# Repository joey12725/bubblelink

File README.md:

# BubbleLink

**A wearable, pack-fed bubble system: one backpack feeds two hand-held bubble guns with power and solution, and a custom analog controller runs the pump only when you pull a trigger.**

Toy bubble guns are fun for about fifteen minutes. Then the AA cells sag, the bottle runs dry, and you are refilling a thimble of solution on a dark dance floor. BubbleLink moves the battery, the solution and the pump into a backpack and turns the guns into lightweight heads on umbilicals. Each umbilical carries power, a fluid line and a load-bearing tether. One 90 Wh pack and one litre of solution run two guns for a whole festival night.

Everything is here: the controller PCB (KiCad, Gerbers, BOM, pick-and-place, verification), every printed part (parametric OpenSCAD and ready-to-slice STLs), a full bill of materials, and build, bring-up and test guides.

| | | |
|:-:|:-:|:-:|
|  |  |  |
| **Duo guns**: a mirrored left/right pair, two blower heads each | **The stick**: battery sled, breaker, BMS and bucks over a draining wet cup | **BubbleLink CTRL v1.2**: 50 × 40 mm analog pump controller |

## Highlights

- **90 Wh 2S5P pack** (10 × Samsung 25R) with a 40 A BMS, USB-C charging, one 30 A manual-reset breaker and a pull-out power key.
- **Automatic pump control.** A Hall sensor sees gun current, a dual comparator turns the pump on, and an RC timer holds it for a tunable ~350 ms after the trigger releases. No firmware, no microcontroller, nothing to flash.
- **Two gun channels** on XT30U, each with its own fluid line and paracord tether. A dropped gun pulls on the cord, never the wires or the hose.
- **One shared peristaltic pump** with a recirculating bypass and check valve, so a stopped gun is never force-fed and the reservoir can't siphon.
- **Built for jumping.** The whole pack is one sealed upright "stick": dry tube on top, draining wet cup below, TPU seals and cushions, and nothing exits underneath.
- **Measured runtime**: about 2 hours of nonstop firing with all four heads, about 8 hours with one, and over 100 hours idle.
- **Verified before fabrication.** 50 automated release checks on the board files and a 20,000-sample Monte Carlo of the analog circuit, both re-runnable from this repo.
- **56 ready-to-slice STLs**, all watertight and designed to print without supports, generated from parametric OpenSCAD.

## How it works

```mermaid
flowchart LR
    subgraph pack["Backpack: the stick"]
        BAT["2S5P 90 Wh<br/>+ 40 A BMS"] --> KEY["Power key<br/>(XT60H)"] --> BRK["30 A breaker"] --> ACS["ACS758<br/>current sensor"]
        ACS --> CH1["Gun port 1<br/>XT30U"]
        ACS --> CH2["Gun port 2<br/>XT30U"]
        BRK --> BUCKA["Buck A 5 V"] --> CTRL["BubbleLink CTRL<br/>analog controller"]
        ACS -. "40 mV/A" .-> CTRL
        CTRL --> PUMP["G528 peristaltic pump"]
        BLAD["1 L bladder"] --> PUMP --> TEE["Tees + bypass<br/>+ check valve"]
    end
    CH1 == "power + hose + tether" ==> G1["Duo gun L"]
    CH2 == "power + hose + tether" ==> G2["Duo gun R"]
    TEE --> G1
    TEE --> G2
```

1. **Pull a trigger.** The gun's motor draws current straight from the battery bus (6.0–8.4 V, unregulated). Gun current never passes through the PCB.
2. **The controller notices.** The ACS758 module reports combined gun current. One half of the TLV1822 comparator flags it against the RV1 threshold.
3. **The pump runs.** Q1 charges a hold capacitor, the second comparator half sees it high and (through Q3) turns on the AO3400A pump MOSFET, and the G528 pushes solution down both umbilicals.
4. **Release the trigger.** The hold capacitor bleeds through RV2, with Schmitt feedback for a clean edge. About 350 ms later the pump stops, so the donor pumps in the heads stay primed without flooding.
5. **Prime on demand.** The PRIME button on the cap runs the same timed path, for filling lines at the start of a night.

Every failure lands on "pump off": a supervisor clamps the timer below 4.38 V, the pump gate defaults low if the comparator is unpowered, a PTC guards the pump branch, and an unplugged sensor reads as no current. The [design description](hardware/pcb/BubbleLink_CTRL_v1_2_PCBWay/customer/DESIGN_DESCRIPTION.md) walks through every net.

## Repository layout

| Path | Contents |
|---|---|
| [`hardware/pcb/BubbleLink_CTRL_v1_2_PCBWay/`](hardware/pcb/BubbleLink_CTRL_v1_2_PCBWay/) | Controller release: KiCad source, Gerbers, SMT BOM/CPL, assembly drawing, schematic, verification |
| [`hardware/pcb/hand_solder_guide/`](hardware/pcb/hand_solder_guide/) | Illustrated guides for the through-hole parts, harness, battery and first power-up |
| [`hardware/printed/`](hardware/printed/README.md) | OpenSCAD sources (`src/`), STLs (`stl/`), renders and the full print guide |
| [`docs/`](docs/canonical-facts.md) | System design, subsystems, build guide, test plan, BOM |
| [`tests/`](tests/) | Release checks run in CI |

## Build one

1. **Get the parts.** Everything is in the [bill of materials](docs/bom.md), with part numbers and supplier search links.
2. **Order the board.** Upload [`BubbleLink_CTRL_v1_2_Gerbers.zip`](hardware/pcb/BubbleLink_CTRL_v1_2_PCBWay/fabrication/BubbleLink_CTRL_v1_2_Gerbers.zip) with the SMT [BOM](hardware/pcb/BubbleLink_CTRL_v1_2_PCBWay/assembly/PCBWAY_SMT_BOM.csv) and [CPL](hardware/pcb/BubbleLink_CTRL_v1_2_PCBWay/assembly/PCBWAY_SMT_CPL.csv) to any fab with top-side assembly. Hand-solder the ten through-hole parts using the [solder guide](hardware/pcb/hand_solder_guide/).
3. **Print the parts.** Start with the fit coupons, then follow the [print order](hardware/printed/README.md#print-order). Rigid parts are ASA, seals and cushions are TPU, and nothing needs supports.
4. **Assemble.** The [build guide](docs/10-build-guide.md) covers cell matching, the 2S5P block, the harness, sled, cup plumbing, umbilicals and the guns.
5. **Bring it up.** Follow the [bring-up and acceptance test](docs/07-pcb/bringup-and-acceptance-test.md) to set the detection threshold (RV1) and the off-delay (RV2), then run the [system test plan](docs/13-test-plan.md).

### Firmware

There isn't any. The controller is pure analog: two trimmers set its behaviour, and a multimeter and a screwdriver are the whole toolchain.

### Rebuilding the printed parts

```sh
cd hardware/printed
./build.sh /path/to/openscad      # regenerates every STL from src/ (OpenSCAD 2024+ with the manifold backend)
python check_stl.py               # watertight, one body, no overhang past 45°
```

## Verify the release

The checks that gate the PCB release and the printed parts run in CI on every push:

```sh
pip install -r requirements-dev.txt
python -m pytest -q
```

That covers the release checksums, the 50-check manufacturing validator (board outline, nets, holes, BOM, CPL, DRC, frozen hashes), the analog model with a Monte Carlo sweep, and watertightness of every STL. The full 20,000-sample run is `python3 hardware/pcb/BubbleLink_CTRL_v1_2_PCBWay/verification/analog_model/run_verification.py`.

## Documentation

**System:** [canonical facts](docs/canonical-facts.md) (the one-page source of truth) · [overview and requirements](docs/01-overview-and-requirements.md) · [architecture](docs/02-system-architecture.md) · [design decisions](docs/03-design-decisions.md) · [glossary](docs/glossary.md)

**Subsystems:** [power](docs/04-power-system.md) · [fluid](docs/05-fluid-system.md) · [guns, heads and umbilicals](docs/06-guns-heads-and-umbilicals.md) · [controller PCB](docs/07-pcb/overview.md) ([pinout](docs/07-pcb/connectors-and-pinout.md), [BOM](docs/07-pcb/bom-and-parts.md), [fabrication](docs/07-pcb/fabrication-and-assembly.md), [bring-up](docs/07-pcb/bringup-and-acceptance-test.md), [revisions](docs/07-pcb/revision-history.md)) · [printed parts](docs/09-printed-parts.md)

**Making it:** [BOM](docs/bom.md) · [build guide](docs/10-build-guide.md) · [test plan](docs/13-test-plan.md) · [roadmap](docs/16-roadmap-future-extensions.md)

## Tech

KiCad 9 · tscircuit · Gerbonara + Shapely geometry checks · Python analog model with Monte Carlo · OpenSCAD (manifold backend) · trimesh · ASA and TPU on a Creality K2 Plus and a Bambu Lab A1

## Safety

This is a 90 Wh lithium pack worn on your back. Build the battery with matched cells, keep the breaker in the + line, charge with the cap off until you have checked enclosed-charging temperature, and follow the bench gates in the test plan before wearing it.

## License

Open hardware. Hardware design files are [CERN-OHL-P-2.0](LICENSES/CERN-OHL-P-2.0.txt), software is [MIT](LICENSES/MIT.txt), and documentation and images are [CC-BY-4.0](LICENSES/CC-BY-4.0.txt). See [LICENSE](LICENSE) for which applies where.

---

Designed and built by **Joey Hersh**.

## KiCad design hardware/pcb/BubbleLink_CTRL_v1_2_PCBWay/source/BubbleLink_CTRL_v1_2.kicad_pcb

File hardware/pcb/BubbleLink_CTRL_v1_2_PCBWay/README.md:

# BubbleLink CTRL v1.2: release package

The complete fabrication release for the BubbleLink pump controller: a 50 × 40 mm, two-layer, all-analog board that runs the pack's transfer pump whenever a gun draws current, then holds it on for a tunable off-delay.

## Ordering boards

Upload these to any PCB fab that does top-side SMT assembly:

| File | Use |
|---|---|
| `fabrication/BubbleLink_CTRL_v1_2_Gerbers.zip` | Gerbers and drills. Upload this ZIP, not the whole folder |
| `assembly/PCBWAY_SMT_BOM.csv` | SMT BOM (41 placements, top side only) |
| `assembly/PCBWAY_SMT_CPL.csv` | Pick-and-place, mm, lower-left datum, top view |
| `assembly/ASSEMBLY_NOTES_FOR_PCBWAY.txt` | Polarity, DNP and substitution rules |
| `drawings/BubbleLink_CTRL_v1_2_Assembly_and_U1_Detail.pdf` | Assembly drawing; its numbered pads and pin-1 table control orientation |
| `assembly/CRITICAL_PAD1_COORDINATES.csv` | Pin-1 coordinates for U1, U2, Q1–Q3, D1 |

J4 and R22 are DNP. C9 and R18 must be fitted. U1 is TI TLV1822QDRQ1 with no substitute. The through-hole parts (`assembly/USER_THT_BOM.csv`) are hand-soldered after delivery; see the [hand-solder guide](../hand_solder_guide/).

## What else is here

- `source/`: KiCad project (`.kicad_pcb`, `.kicad_sch`, `.kicad_pro`, also zipped), the serialized tscircuit design, and `repro/`, the deterministic engineering-change scripts that turn the v1.1 baseline into v1.2.
- `drawings/`: schematic and PCB SVGs and independently parsed Gerber previews.
- `customer/`: design description, bring-up and acceptance test, motor harness suppression.
- `verification/`: the analog model with Monte Carlo, the manufacturing QA validator, DRC results and geometry regression.
- `ENGINEERING_CHANGE_AND_REVIEW.md`: why v1.2 exists (the corrected U1 land pattern, per TI D0008A) and what changed.
- `SHA256SUMS.txt`: checksums for every file in this folder.

## Re-running the checks

```sh
python3 verification/manufacturing_qa/validate_release.py --help   # or:
bash verification/run_release_qa.sh                                  # 50 structural checks
python3 verification/analog_model/run_verification.py               # model + 20,000-sample Monte Carlo
python3 verification/verify_eco.py                                   # needs gerbonara + shapely
```

The automated checks cover structure, geometry and the circuit model. Startup, brownout, timing calibration, sensor noise and thermal behaviour are covered by the bench procedure in `customer/BRINGUP_AND_ACCEPTANCE_TEST.md`.

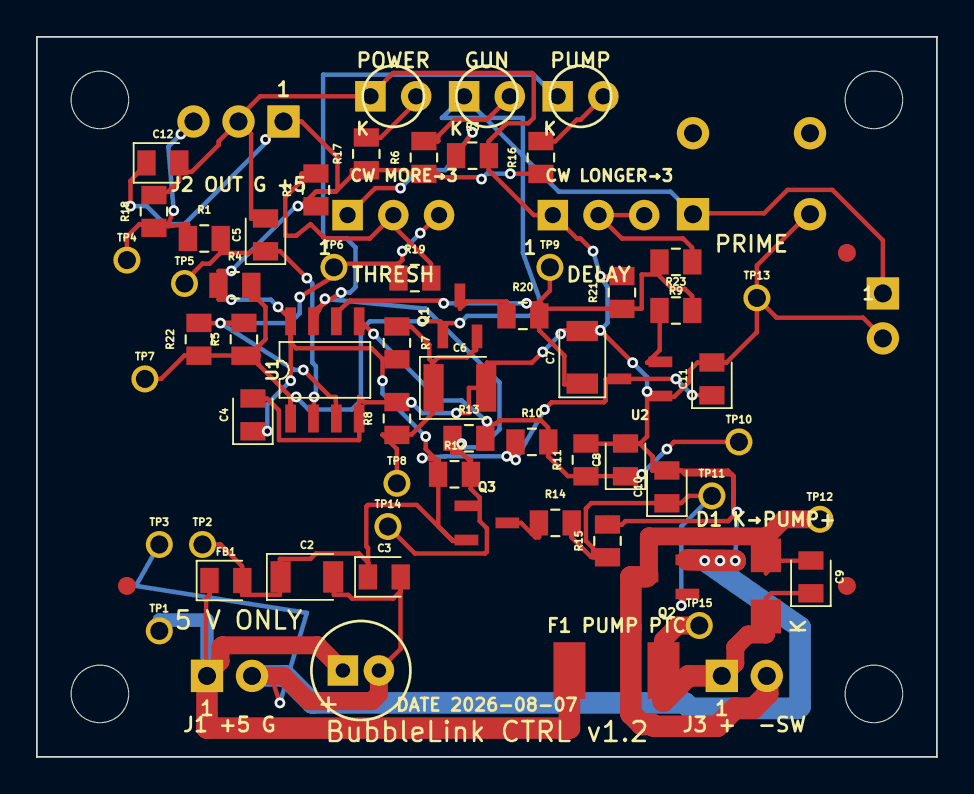
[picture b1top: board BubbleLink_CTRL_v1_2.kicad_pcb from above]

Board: 2 copper layers, 50.0 x 40.0 mm, 68 parts (0 on the bottom side), 23 nets.

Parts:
C1: 16ZLH100MEFC5X11
C2: 10uF; GRM31CR71C106KA12L
C3, C4, C8, C9, C10, C11, C12: 100nF; GRM21BR71H104KA01L
C5: 1uF; GRM21BR71C105KA01L
C6: 22uF; C3225X7R1E226M250AB
C7: 6.8uF; CGA5L1X7R1E685K160AC
D1: B340A-E3/61T; B340A-E3_61T
F1: F1; 1812L150_16DR
FB1: BLM21PG221SN1D
J1, J3: B2B-XH-A(LF)(SN)
J2: B3B-XH-A(LF)(SN)
J4: chip
LED1: L-934GD
LED2: L-934YD
LED3: L-934ID
Q1, Q3: DMP2065UQ-7
Q2: AO3400A
R1, R4, R9, R11, R12, R15: 10kΩ; RC0805FR-0710KL
R2, R3: 7.5kΩ; RC0805FR-077K5L
R5, R13, R22: 4.7MΩ; RC0805FR-074M7L
R6, R16, R17, R20: 2.2kΩ; RC0805FR-072K2L
R7, R8: 4.7kΩ; RC0805FR-074K7L
R10: 39kΩ; RC0805FR-0739KL
R14: 100Ω; RC0805FR-07100RL
R18: 100kΩ; RC0805FR-07100KL
R19: 220kΩ; RC0805FR-07220KL
R21: 1MΩ; RC0805FR-071ML
R23: 560Ω; RC0805FR-07560RL
RV1: 3296W-1-202LF
RV2: 3296W-1-104LF
SW1: B3F-1000
TP1: TP1; test_point_platedhole_d1
TP2: TP2; test_point_platedhole_d1
TP3: TP3; test_point_platedhole_d1
TP4: TP4; test_point_platedhole_d1
TP5: TP5; test_point_platedhole_d1
TP6: TP6; test_point_platedhole_d1
TP7: TP7; test_point_platedhole_d1
TP8: TP8; test_point_platedhole_d1
TP9: TP9; test_point_platedhole_d1
TP10: TP10; test_point_platedhole_d1
TP11: TP11; test_point_platedhole_d1
TP12: TP12; test_point_platedhole_d1
TP13: TP13; test_point_platedhole_d1
TP14: TP14; test_point_platedhole_d1
TP15: TP15; test_point_platedhole_d1
U1: TLV1822QDRQ1
U2: TLV803EA43DBZR

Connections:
.F1 > .pin2 to .J3 > .pin1: C9.1, D1.1, F1.2, J3.1, TP15.1
.FB1 > .pin2 to .C2 > .pin1: C2.1, C3.1, C4.1, C11.1, C12.1, FB1.2, J2.1, Q3.2, R2.1, R4.1, R6.1, R7.1, R10.1, R12.1, R16.1, R17.1, TP2.1, U1.8, U2.3
.J1 > .pin1 to .F1 > .pin1: C1.1, F1.1, FB1.1, J1.1, TP1.1
.J1 > .pin2 to .Q2 > .pin2: C1.2, C2.2, C3.2, C4.2, C5.2, C6.2, C7.2, C8.2, C10.2, C11.2, C12.2, J1.2, J2.2, J4.2, LED1.1, Q2.2, R3.2, R8.2, R11.2, R15.2, R18.2, R21.2, RV2.1, SW1.3, TP3.1, TP13.1, U1.4, U2.1
.J2 > .pin3 to .R18 > .pin1: J2.3, R1.1, R18.1, TP4.1
.Q1 > .pin3 to .R20 > .pin1: Q1.3, R20.1
.Q2 > .pin3 to .J3 > .pin2: C9.2, D1.2, J3.2, Q2.3, TP12.1
.Q3 > .pin3 to .R14 > .pin1: Q3.3, R14.1
.R1 > .pin2 to .C5 > .pin1: C5.1, R1.2, TP5.1, U1.2
.R2 > .pin2 to .RV1 > .pin3: R2.2, R19.2, RV1.3
.R6 > .pin2 to .LED2 > .pin2: LED2.2, R6.2
.R7 > .pin2 to .C6 > .pin1: C6.1, Q1.2, R7.2, R8.1, TP8.1
.R9 > .pin2 to .RV2 > .pin3: R9.2, RV2.2, RV2.3
.R14 > .pin2 to .R15 > .pin1: C10.1, Q2.1, R14.2, R15.1, TP11.1
.R16 > .pin2 to .LED3 > .pin2: LED3.2, R16.2
.R17 > .pin2 to .LED1 > .pin2: LED1.2, R17.2
.RV1 > .pin1 to .R3 > .pin1: R3.1, RV1.1
.RV1 > .pin2 to .R19 > .pin1: R5.2, R19.1, R22.2, RV1.2, TP6.1, U1.3
.U1 > .pin1 to .R5 > .pin1: J4.1, LED2.1, Q1.1, R4.2, R5.1, R22.1, SW1.1, TP7.1, U1.1
.U1 > .pin5 to .R13 > .pin2: C8.1, R10.2, R11.1, R13.2, TP10.1, U1.5
.U1 > .pin6 to .R20 > .pin2: C7.1, R9.1, R20.2, R21.1, R23.2, TP9.1, U1.6
.U1 > .pin7 to .R13 > .pin1: LED3.1, Q3.1, R12.2, R13.1, TP14.1, U1.7
.U2 > .pin2 to .R23 > .pin1: R23.1, U2.2

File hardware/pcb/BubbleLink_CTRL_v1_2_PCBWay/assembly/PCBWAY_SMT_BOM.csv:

Item,Reference Designator,Quantity,Manufacturer,Manufacturer Part Number,Description,Package or Footprint,Layer,Substitution
1,U1,1,Texas Instruments,TLV1822QDRQ1,Dual open-drain comparator,SOIC-8,Top,NO SUBSTITUTE
2,U2,1,Texas Instruments,TLV803EA43DBZR,"4.38 V 200 ms supply supervisor; default DBZ pinout",SOT-23-3 DBZ,Top,NO SUBSTITUTE
3,"Q1,Q3",2,Diodes Incorporated,DMP2065UQ-7,P-channel MOSFET,SOT-23,Top,NO SUBSTITUTE WITHOUT WRITTEN APPROVAL
4,Q2,1,Alpha & Omega Semiconductor,AO3400A,N-channel MOSFET,SOT-23,Top,NO SUBSTITUTE WITHOUT WRITTEN APPROVAL
5,D1,1,Vishay,B340A-E3/61T,3 A 40 V Schottky diode,SMA DO-214AC custom manufacturer land pattern,Top,NO SUBSTITUTE
6,F1,1,Littelfuse,1812L150/16DR,"1.50 A hold 16 V resettable PTC",1812 custom manufacturer land pattern,Top,NO SUBSTITUTE
7,FB1,1,Murata,BLM21PG221SN1D,220 ohm at 100 MHz ferrite bead,0805,Top,NO SUBSTITUTE WITHOUT WRITTEN APPROVAL
8,C2,1,Murata,GRM31CR71C106KA12L,10 uF 16 V X7R 10%,1206,Top,NO SUBSTITUTE WITHOUT WRITTEN APPROVAL
9,"C3,C4,C8,C9,C10,C11,C12",7,Murata,GRM21BR71H104KA01L,100 nF 50 V X7R 10%,0805,Top,EQUIVALENT ALLOWED
10,C5,1,Murata,GRM21BR71C105KA01L,1 uF 16 V X7R 10%,0805,Top,EQUIVALENT ALLOWED
11,C6,1,TDK,C3225X7R1E226M250AB,22 uF 25 V X7R 20%,1210,Top,NO SUBSTITUTE WITHOUT WRITTEN APPROVAL
12,C7,1,TDK,CGA5L1X7R1E685K160AC,6.8 uF 25 V X7R 10%,1206,Top,NO SUBSTITUTE WITHOUT WRITTEN APPROVAL
13,R14,1,Yageo,RC0805FR-07100RL,100 ohm 1%,0805,Top,EQUIVALENT ALLOWED
14,R23,1,Yageo,RC0805FR-07560RL,560 ohm 1%,0805,Top,EQUIVALENT ALLOWED
15,"R6,R16,R17,R20",4,Yageo,RC0805FR-072K2L,2.2 kohm 1%,0805,Top,EQUIVALENT ALLOWED
16,"R7,R8",2,Yageo,RC0805FR-074K7L,4.7 kohm 1%,0805,Top,EQUIVALENT ALLOWED
17,"R2,R3",2,Yageo,RC0805FR-077K5L,7.5 kohm 1%,0805,Top,EQUIVALENT ALLOWED
18,"R1,R4,R9,R11,R12,R15",6,Yageo,RC0805FR-0710KL,10 kohm 1%,0805,Top,EQUIVALENT ALLOWED
19,R10,1,Yageo,RC0805FR-0739KL,39 kohm 1%,0805,Top,EQUIVALENT ALLOWED
20,R18,1,Yageo,RC0805FR-07100KL,100 kohm 1% required ACS pulldown,0805,Top,EQUIVALENT ALLOWED BUT MUST BE FITTED
21,R19,1,Yageo,RC0805FR-07220KL,220 kohm 1%,0805,Top,EQUIVALENT ALLOWED
22,R21,1,Yageo,RC0805FR-071ML,1 Mohm 1%,0805,Top,EQUIVALENT ALLOWED
23,"R5,R13",2,Yageo,RC0805FR-074M7L,4.7 Mohm 1%,0805,Top,EQUIVALENT ALLOWED
